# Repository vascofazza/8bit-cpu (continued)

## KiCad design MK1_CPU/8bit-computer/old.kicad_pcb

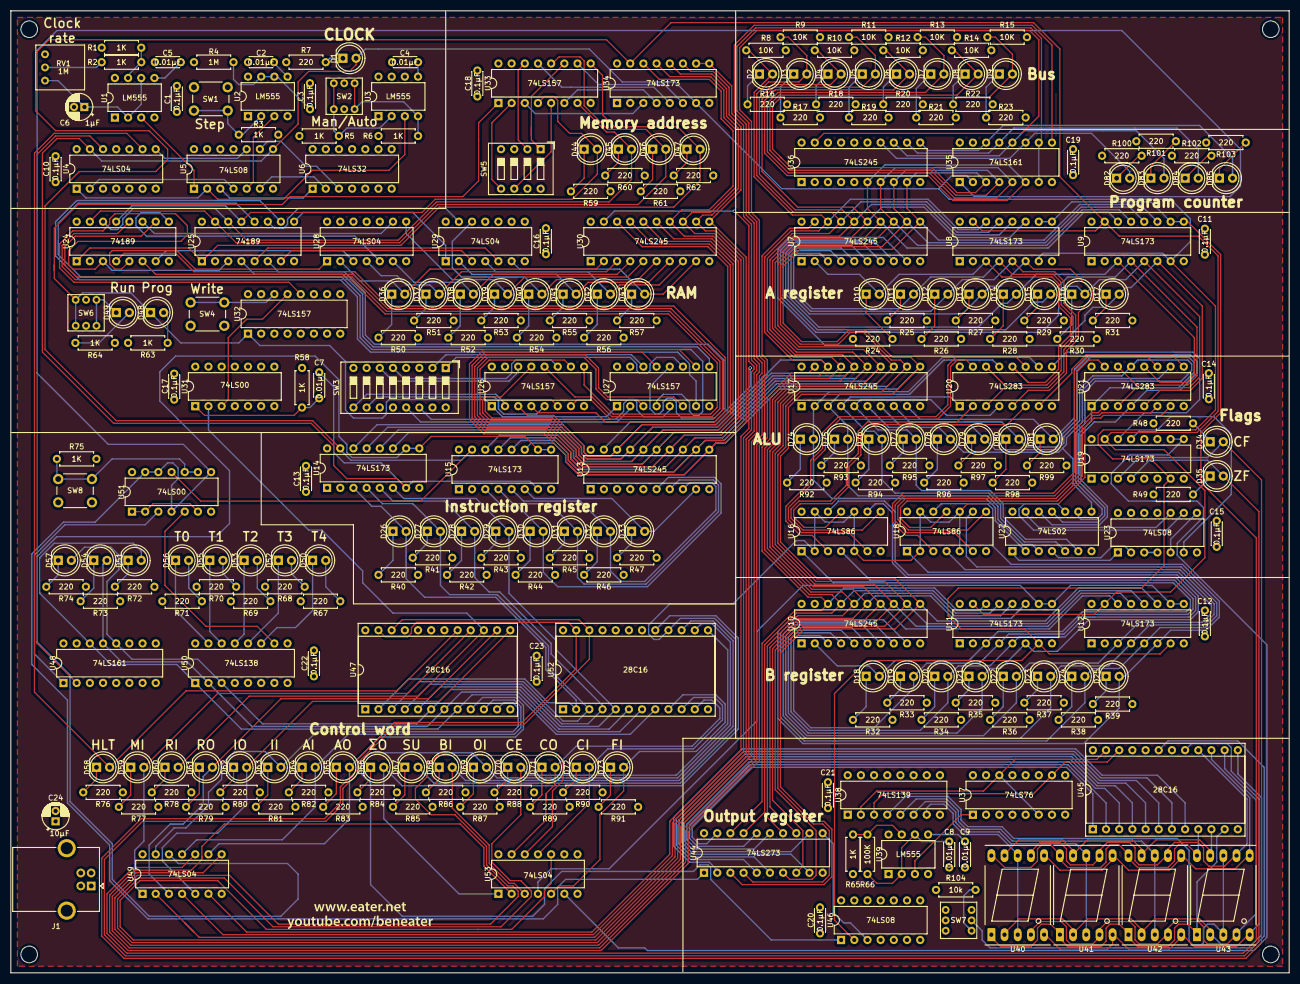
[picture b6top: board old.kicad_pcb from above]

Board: 4 copper layers, 246.4 x 185.4 mm, 277 parts (0 on the bottom side), 290 nets.

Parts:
C1, C3, C10, C11, C12, C13, C14, C15, C16, C17, C18, C19, C20, C21, C22, C23: 0.1µF; C_Disc_D4.3mm_W1.9mm_P5.00mm
C2, C4, C5, C7, C8, C9: 0.01µF; C_Disc_D4.3mm_W1.9mm_P5.00mm
C6: 1µF; CP_Radial_D5.0mm_P2.00mm
C24: 10µF; CP_Radial_D5.0mm_P2.00mm
D1, D26, D27, D28, D29, D58, D59, D60, D61, D62, D63, D64, D65, D66, D67, D68, D69, D70, D71, D72, D73: BLUE; LED_D5.0mm
D2, D3, D4, D5, D6, D7, D8, D9, D10, D11, D12, D13, D14, D15, D16, D17, D18, D19, D20, D21, D22, D23, D24, D25, D36, D37, D38, D39, D40, D41, D42, D43, D48, D51, D54, D57, D74, D75, D76, D77, D78, D79, D80, D81: RED; LED_D5.0mm
D30, D31, D32, D33, D44, D45, D46, D47: YELLOW; LED_D5.0mm
D34, D35, D49, D50, D52, D53, D55, D56, D82, D83, D84, D85: GREEN; LED_D5.0mm
J1: USB_B; USB_B_OST_USB-B1HSxx_Horizontal
R1, R2, R3, R5, R6, R58, R63, R64, R65, R75: 1K; R_Axial_DIN0207_L6.3mm_D2.5mm_P7.62mm_Horizontal
R4: 1M; R_Axial_DIN0207_L6.3mm_D2.5mm_P7.62mm_Horizontal
R7, R16, R17, R18, R19, R20, R21, R22, R23, R24, R25, R26, R27, R28, R29, R30, R31, R32, R33, R34, R35, R36, R37, R38, R39, R40, R41, R42, R43, R44, R45, R46, R47, R48, R49, R50, R51, R52, R53, R54, R55, R56, R57, R59, R60, R61, R62, R67, R68, R69, R70, R71, R72, R73, R74, R76, R77, R78, R79, R80, R81, R82, R83, R84, R85, R86, R87, R88, R89, R90, R91, R92, R93, R94, R95, R96, R97, R98, R99, R100, R101, R102, R103: 220; R_Axial_DIN0207_L6.3mm_D2.5mm_P7.62mm_Horizontal
R8, R9, R10, R11, R12, R13, R14, R15: 10K; R_Axial_DIN0207_L6.3mm_D2.5mm_P7.62mm_Horizontal
R66: 100K; R_Axial_DIN0207_L6.3mm_D2.5mm_P7.62mm_Horizontal
R104: 10k; R_Axial_DIN0207_L6.3mm_D2.5mm_P7.62mm_Horizontal
RV1: 1M; Potentiometer-5.5mm
SW1, SW4: SW_Push; SW_PUSH_6mm_H5mm
SW2, SW6, SW7: SW_SPDT; DPDT-pushbutton
SW3: SW_DIP_x08; SW_DIP_SPSTx08_Slide_9.78x22.5mm_W7.62mm_P2.54mm
SW5: SW_DIP_x04; SW_DIP_SPSTx04_Slide_9.78x12.34mm_W7.62mm_P2.54mm
SW8: Reset; SW_PUSH_6mm_H5mm
U1, U2, U3, U39: LM555; DIP-8_W7.62mm
U4, U28, U29, U49, U53: 74LS04; DIP-14_W7.62mm
U5, U23, U46: 74LS08; DIP-14_W7.62mm
U6: 74LS32; DIP-14_W7.62mm
U7, U10, U13, U17, U30, U36: 74LS245; DIP-20_W7.62mm
U8, U9, U11, U12, U14, U15, U19, U34: 74LS173; DIP-16_W7.62mm
U16, U18: 74LS86; DIP-14_W7.62mm
U20, U21: 74LS283; DIP-16_W7.62mm
U22: 74LS02; DIP-14_W7.62mm
U24, U25: 74189; DIP-16_W7.62mm
U26, U27, U32, U33: 74LS157; DIP-16_W7.62mm
U31, U51: 74LS00; DIP-14_W7.62mm
U35, U48: 74LS161; DIP-16_W7.62mm
U37: 74LS76; DIP-16_W7.62mm
U38: 74LS139; DIP-16_W7.62mm
U40, U41, U42, U43: 7SEGMENT_CC; 7SegmentLED_LTS6760_LTS6780
U44: 74LS273; DIP-20_W7.62mm
U45, U47, U52: 28C16; DIP-24_W15.24mm_Socket
U50: 74LS138; DIP-16_W7.62mm
svg2mod: G***; BenEater

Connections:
/A register/A_0: D17.2, U7.9, U9.6, U21.5
/A register/A_1: D16.2, U7.8, U9.5, U21.3
/A register/A_2: D15.2, U7.7, U9.4, U21.14
/A register/A_3: D14.2, U7.6, U9.3, U21.12
/A register/A_4: D13.2, U7.5, U8.6, U20.5
/A register/A_5: D12.2, U7.4, U8.5, U20.3
/A register/A_6: D11.2, U7.3, U8.4, U20.14
/A register/A_7: D10.2, U7.2, U8.3, U20.12
/A register/BUS_0: D9.2, R15.1, U7.11, U9.11, U10.11, U12.11, U13.11, U15.11, U17.11, U27.10, U30.11, U34.11, U35.3, U36.9, U44.3
/A register/BUS_1: D8.2, R14.1, U7.12, U9.12, U10.12, U12.12, U13.12, U15.12, U17.12, U27.13, U30.12, U34.12, U35.4, U36.8, U44.4
/A register/BUS_2: D7.2, R13.1, U7.13, U9.13, U10.13, U12.13, U13.13, U15.13, U17.13, U27.6, U30.13, U34.13, U35.5, U36.7, U44.7
/A register/BUS_3: D6.2, R12.1, U7.14, U9.14, U10.14, U12.14, U13.14, U15.14, U17.14, U27.3, U30.14, U34.14, U35.6, U36.6, U44.8
/A register/BUS_4: D5.2, R11.1, U7.15, U8.11, U10.15, U11.11, U13.15, U14.11, U17.15, U26.10, U30.15, U44.13
/A register/BUS_5: D4.2, R10.1, U7.16, U8.12, U10.16, U11.12, U13.16, U14.12, U17.16, U26.13, U30.16, U44.14
/A register/BUS_6: D3.2, R9.1, U7.17, U8.13, U10.17, U11.13, U13.17, U14.13, U17.17, U26.6, U30.17, U44.17
/A register/BUS_7: D2.2, R8.1, U7.18, U8.14, U10.18, U11.14, U13.18, U14.14, U17.18, U26.3, U30.18, U44.18
/A register/CLK: C7.1, D1.2, U4.13, U5.8, U8.7, U9.7, U11.7, U12.7, U14.7, U15.7, U19.7, U34.7, U35.2, U46.2
/A register/CLR: U8.15, U9.15, U11.15, U12.15, U14.15, U15.15, U19.15, U34.15, U51.11
/A register/~AI: U8.9, U8.10, U9.9, U9.10, U49.10
/A register/~AO: U7.19, U49.8
/ALU/B_0: D25.2, U10.9, U12.6, U18.12
/ALU/B_1: D24.2, U10.8, U12.5, U18.9
/ALU/B_2: D23.2, U10.7, U12.4, U18.4
/ALU/B_3: D22.2, U10.6, U12.3, U18.1
/ALU/B_4: D21.2, U10.5, U11.6, U16.12
/ALU/B_5: D20.2, U10.4, U11.5, U16.9
/ALU/B_6: D19.2, U10.3, U11.4, U16.4
/ALU/B_7: D18.2, U10.2, U11.3, U16.1
/ALU/CF: D34.2, U19.3, U47.23, U52.23
/ALU/SU: D67.2, U16.2, U16.5, U16.10, U16.13, U18.2, U18.5, U18.10, U18.13, U21.7, U52.16
/ALU/ZF: D35.2, U19.4, U47.22, U52.22
/ALU/~EO: U17.19, U53.2
/ALU/~FI: U19.9, U19.10, U53.6
/B register/~BI: U11.9, U11.10, U12.9, U12.10, U53.4
/Clock/HLT: D58.2, U4.9, U47.17
/Clock/~CLK: U4.12, U48.2
/Control logic/CE: D70.2, U35.7, U35.10, U52.13
/Control logic/IR_4: D29.2, U14.6, U47.5, U52.5
/Control logic/IR_5: D28.2, U14.5, U47.4, U52.4
/Control logic/IR_6: D27.2, U14.4, U47.3, U52.3
/Control logic/IR_7: D26.2, U14.3, U47.2, U52.2
/Control logic/OI: D69.2, U46.1, U52.14
/Control logic/RI: D60.2, U31.2, U47.15
/Control logic/~CLR: U35.1, U44.1, U51.4, U51.8, U51.12, U51.13
/Control logic/~CO: U36.19, U53.12
/Control logic/~II: U14.9, U14.10, U15.9, U15.10, U49.12
/Control logic/~IO: U13.19, U49.6
/Control logic/~J: U35.9, U53.10
/Control logic/~MI: U34.9, U34.10, U49.2
/Control logic/~RO: U30.19, U49.4
/MAR/A0: D47.2, U24.1, U25.1, U33.9
/MAR/A1: D46.2, U24.15, U25.15, U33.12
/MAR/A2: D45.2, U24.14, U25.14, U33.7
/MAR/A3: D44.2, U24.13, U25.13, U33.4
/MAR/PROG: D48.1, SW6.1, U26.1, U27.1, U32.1, U33.1
GND: C1.2, C2.2, C3.2, C4.2, C5.2, C6.2, C8.2, C9.2, C10.2, C11.2, C12.2, C13.2, C14.2, C15.2, C16.2, C17.2, C18.2, C19.2, C20.2, C21.2, C22.2, C23.2, C24.2, J1.4, J1.5, R7.2, R8.2, R9.2, R10.2, R11.2, R12.2, R13.2, R14.2, R15.2, R16.2, R17.2, R18.2, R19.2, R20.2, R21.2, R22.2, R23.2, R24.2, R25.2, R26.2, R27.2, R28.2, R29.2, R30.2, R31.2, R32.2, R33.2, R34.2, R35.2, R36.2, R37.2, R38.2, R39.2, R40.2, R41.2, R42.2, R43.2, R44.2, R45.2, R46.2, R47.2, R48.1, R49.1, R50.2, R51.2, R52.2, R53.2, R54.2, R55.2, R56.2, R57.2, R58.1, R59.2, R60.2, R61.2, R62.2, R72.2, R73.2, R74.2, R75.2, R76.2, R77.2, R78.2, R79.2, R80.2, R81.2, R82.2, R83.2, R84.2, R85.2, R86.2, R87.2, R88.2, R89.2, R90.2, R91.2, R92.2, R93.2, R94.2, R95.2, R96.2, R97.2, R98.2, R99.2, R100.1, R101.1, R102.1, R103.1, R104.2, SW1.1, SW2.2, SW3.3, SW3.4, SW3.7, SW3.8, SW3.11, SW3.12, SW3.15, SW3.16, SW4.1, SW5.3, SW5.4, SW5.7, SW5.8, SW6.2, U1.1, U2.1, U3.1, U3.6, U4.7, U5.7, U6.7, U7.10, U8.1, U8.2, U8.8, U9.1, U9.2, U9.8, U10.10, U11.1, U11.2, U11.8, U12.1, U12.2, U12.8, U13.2, U13.3, U13.4, U13.5, U13.10, U14.1, U14.2, U14.8, U15.1, U15.2, U15.8, U16.7, U17.10, U18.7, U19.1, U19.2, U19.8, U20.8, U21.8, U22.7, U23.7, U24.2, U24.8, U25.2, U25.8, U26.8, U26.15, U27.8, U27.15, U28.7, U29.7, U30.10, U31.7, U32.8, U32.15, U33.8, U33.15, U34.1, U34.2, U34.8, U35.8, U36.1, U36.10, U37.13, U38.1, U38.8, U39.1, U44.10, U45.12, U45.18, U45.20, U46.7, U47.1, U47.12, U47.18, U47.19, U47.20, U48.8, U49.7, U50.4, U50.5, U50.8, U51.7, U52.12, U52.18, U52.19, U52.20, U53.7
unnamed: C2.1, U2.5
unnamed: C3.1, R4.2, U2.6, U2.7
unnamed: C4.1, U3.5
unnamed: C5.1, U1.5
unnamed: C6.1, RV1.1, U1.2, U1.6
unnamed: C7.2, R58.2, U31.1
unnamed: C8.1, R66.2, U39.2, U39.6
unnamed: C9.1, U39.5
unnamed: D1.1, R7.1
unnamed: D2.1, R16.1
unnamed: D3.1, R17.1
unnamed: D4.1, R18.1
unnamed: D5.1, R19.1
unnamed: D6.1, R20.1
unnamed: D7.1, R21.1
unnamed: D8.1, R22.1
unnamed: D9.1, R23.1
unnamed: D10.1, R24.1
unnamed: D11.1, R25.1
unnamed: D12.1, R26.1
unnamed: D13.1, R27.1
unnamed: D14.1, R28.1
unnamed: D15.1, R29.1
unnamed: D16.1, R30.1
unnamed: D17.1, R31.1
unnamed: D18.1, R32.1
unnamed: D19.1, R33.1
unnamed: D20.1, R34.1
unnamed: D21.1, R35.1
unnamed: D22.1, R36.1
unnamed: D23.1, R37.1
unnamed: D24.1, R38.1
unnamed: D25.1, R39.1
unnamed: D26.1, R40.1
unnamed: D27.1, R41.1
unnamed: D28.1, R42.1
unnamed: D29.1, R43.1
unnamed: D30.1, R44.1
unnamed: D30.2, U13.6, U15.3
unnamed: D31.1, R45.1
unnamed: D31.2, U13.7, U15.4
unnamed: D32.1, R46.1
unnamed: D32.2, U13.8, U15.5
unnamed: D33.1, R47.1
unnamed: D33.2, U13.9, U15.6
unnamed: D34.1, R48.2
unnamed: D35.1, R49.2
unnamed: D36.1, R50.1
unnamed: D36.2, U28.2, U30.2
unnamed: D37.1, R51.1
unnamed: D37.2, U28.4, U30.3
unnamed: D38.1, R52.1
unnamed: D38.2, U28.6, U30.4
unnamed: D39.1, R53.1
unnamed: D39.2, U28.8, U30.5
unnamed: D40.1, R54.1
unnamed: D40.2, U29.12, U30.6
unnamed: D41.1, R55.1
unnamed: D41.2, U29.2, U30.7
unnamed: D42.1, R56.1
unnamed: D42.2, U29.4, U30.8
unnamed: D43.1, R57.1
unnamed: D43.2, U29.6, U30.9
unnamed: D44.1, R59.1
unnamed: D45.1, R60.1
unnamed: D46.1, R61.1
unnamed: D47.1, R62.1
unnamed: D48.2, R63.2
unnamed: D49.1, SW6.3
unnamed: D49.2, R64.2
unnamed: D50.1, U50.11
unnamed: D50.2, R67.2
unnamed: D51.1, R72.1
unnamed: D51.2, U47.8, U48.14, U50.1, U52.8
unnamed: D52.1, U50.12
unnamed: D52.2, R68.2
unnamed: D53.1, U50.13
unnamed: D53.2, R69.2
unnamed: D54.1, R73.1
unnamed: D54.2, U47.7, U48.13, U50.2, U52.7
unnamed: D55.1, U50.14
unnamed: D55.2, R70.2
unnamed: D56.1, U50.15
unnamed: D56.2, R71.2
unnamed: D57.1, R74.1
unnamed: D57.2, U47.6, U48.12, U50.3, U52.6
unnamed: D58.1, R76.1
unnamed: D59.1, R77.1
unnamed: D59.2, U47.16, U49.1
unnamed: D60.1, R78.1
unnamed: D61.1, R79.1
unnamed: D61.2, U47.14, U49.3
unnamed: D62.1, R80.1
unnamed: D62.2, U47.13, U49.5
unnamed: D63.1, R81.1
unnamed: D63.2, U47.11, U49.13
unnamed: D64.1, R82.1
unnamed: D64.2, U47.10, U49.11
unnamed: D65.1, R83.1
unnamed: D65.2, U47.9, U49.9
unnamed: D66.1, R84.1
unnamed: D66.2, U52.17, U53.1
unnamed: D67.1, R85.1
unnamed: D68.1, R86.1
unnamed: D68.2, U52.15, U53.3
unnamed: D69.1, R87.1
unnamed: D70.1, R88.1
unnamed: D71.1, R89.1
unnamed: D71.2, U52.11, U53.13
unnamed: D72.1, R90.1
unnamed: D72.2, U52.10, U53.11
unnamed: D73.1, R91.1
unnamed: D73.2, U52.9, U53.5
unnamed: D74.1, R92.1
unnamed: D74.2, U17.2, U20.10, U22.2
unnamed: D75.1, R93.1
unnamed: D75.2, U17.3, U20.13, U22.3
unnamed: D76.1, R94.1
unnamed: D76.2, U17.4, U20.1, U22.5
unnamed: D77.1, R95.1
unnamed: D77.2, U17.5, U20.4, U22.6
unnamed: D78.1, R96.1
unnamed: D78.2, U17.6, U21.10, U22.8
unnamed: D79.1, R97.1
unnamed: D79.2, U17.7, U21.13, U22.9
unnamed: D80.1, R98.1
unnamed: D80.2, U17.8, U21.1, U22.11
unnamed: D81.1, R99.1
unnamed: D81.2, U17.9, U21.4, U22.12
unnamed: D82.1, R100.2
unnamed: D82.2, U35.11, U36.14
unnamed: D83.1, R101.2
unnamed: D83.2, U35.12, U36.13
unnamed: D84.1, R102.2
unnamed: D84.2, U35.13, U36.12
unnamed: D85.1, R103.2
unnamed: D85.2, U35.14, U36.11
unnamed: R1.2, R2.2, U1.7
unnamed: R2.1, RV1.2
unnamed: R3.2, SW1.2, U2.2
unnamed: R5.2, SW2.1, U3.2
unnamed: R6.2, SW2.3, U3.4
unnamed: R65.2, R66.1, U39.7
unnamed: R75.1, SW8.1, U51.9, U51.10
unnamed: R104.1, SW7.1
unnamed: SW3.1, U27.11
unnamed: SW3.2, U27.14
unnamed: SW3.5, U26.11
unnamed: SW3.6, U26.14
unnamed: SW3.9, U26.2
unnamed: SW3.10, U26.5
unnamed: SW3.13, U27.2
unnamed: SW3.14, U27.5
unnamed: SW4.2, U32.14
unnamed: SW5.1, U33.11
unnamed: SW5.2, U33.14
unnamed: SW5.5, U33.2
unnamed: SW5.6, U33.5
unnamed: SW7.2, U45.19
unnamed: U1.3, U5.1
unnamed: U2.3, U5.5
unnamed: U3.3, U4.1, U5.2
unnamed: U4.2, U5.4
unnamed: U4.8, U5.10
unnamed: U5.3, U6.1
unnamed: U5.6, U6.2
unnamed: U5.9, U6.3
unnamed: U16.3, U20.11
unnamed: U16.6, U20.15
unnamed: U16.8, U20.2
unnamed: U16.11, U20.6
unnamed: U18.3, U21.11
unnamed: U18.6, U21.15
unnamed: U18.8, U21.2
unnamed: U18.11, U21.6
unnamed: U19.13, U23.6
unnamed: U19.14, U20.9
unnamed: U20.7, U21.9
unnamed: U22.1, U23.1
unnamed: U22.4, U23.2
unnamed: U22.10, U23.9
unnamed: U22.13, U23.10
unnamed: U23.3, U23.4
unnamed: U23.5, U23.8
unnamed: U24.3, U25.3, U32.12
unnamed: U24.4, U26.4
unnamed: U24.5, U28.1
unnamed: U24.6, U26.7
unnamed: U24.7, U28.3
unnamed: U24.9, U28.5
unnamed: U24.10, U26.12
unnamed: U24.11, U28.9
unnamed: U24.12, U26.9
unnamed: U25.4, U27.9
unnamed: U25.5, U29.5
unnamed: U25.6, U27.12
unnamed: U25.7, U29.3
unnamed: U25.9, U29.1
unnamed: U25.10, U27.7
unnamed: U25.11, U29.13
unnamed: U25.12, U27.4
unnamed: U31.3, U32.13
unnamed: U33.3, U34.3
unnamed: U33.6, U34.4
unnamed: U33.10, U34.6
unnamed: U33.13, U34.5
unnamed: U37.1, U39.3
unnamed: U37.10, U38.3, U45.22
unnamed: U37.6, U37.14, U38.2, U45.23
unnamed: U38.4, U43.3, U43.8
unnamed: U38.5, U42.3, U42.8
unnamed: U38.6, U41.3, U41.8
unnamed: U38.7, U40.3, U40.8
unnamed: U40.1, U41.1, U42.1, U43.1, U45.11
unnamed: U40.2, U41.2, U42.2, U43.2, U45.13
unnamed: U40.4, U41.4, U42.4, U43.4, U45.14
unnamed: U40.5, U41.5, U42.5, U43.5, U45.17
unnamed: U40.6, U41.6, U42.6, U43.6, U45.15
unnamed: U40.7, U41.7, U42.7, U43.7, U45.16
unnamed: U40.9, U41.9, U42.9, U43.9, U45.10
unnamed: U40.10, U41.10, U42.10, U43.10, U45.9
unnamed: U44.2, U45.8
unnamed: U44.5, U45.7
unnamed: U44.6, U45.6
unnamed: U44.9, U45.5
unnamed: U44.11, U46.3
unnamed: U44.12, U45.4
unnamed: U44.15, U45.3
unnamed: U44.16, U45.2
unnamed: U44.19, U45.1
unnamed: U48.1, U51.3
unnamed: U50.10, U51.5
unnamed: U51.1, U51.2, U51.6
VCC: C1.1, C10.1, C11.1, C12.1, C13.1, C14.1, C15.1, C16.1, C17.1, C18.1, C19.1, C20.1, C21.1, C22.1, C23.1, C24.1, J1.1, R1.1, R3.1, R4.1, R5.1, R6.1, R63.1, R64.1, R65.1, R67.1, R68.1, R69.1, R70.1, R71.1, SW7.3, SW8.2, U1.4, U1.8, U2.4, U2.8, U3.8, U4.14, U5.14, U6.14, U7.1, U7.20, U8.16, U9.16, U10.1, U10.19, U10.20, U11.16, U12.16, U13.1, U13.20, U14.16, U15.16, U16.14, U17.1, U17.20, U18.14, U19.16, U20.16, U21.16, U22.14, U23.14, U24.16, U25.16, U26.16, U27.16, U28.14, U29.14, U30.1, U30.20, U31.14, U32.16, U33.16, U34.16, U35.16, U36.20, U37.2, U37.3, U37.4, U37.5, U37.7, U37.8, U37.9, U37.12, U37.16, U38.16, U39.8, U44.20, U45.21, U45.24, U46.14, U47.21, U47.24, U48.7, U48.9, U48.10, U48.16, U49.14, U50.6, U50.16, U51.14, U52.1, U52.21, U52.24, U53.14

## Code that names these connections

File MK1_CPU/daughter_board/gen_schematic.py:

#!/usr/bin/env python3
"""Generate KiCad 8 schematic for MK1 I2C/SPI/Speaker daughter board."""
import uuid

def uid():
    return str(uuid.uuid4())

# Component positions (mm)
J4_X, J4_Y = 30, 80
U1_X, U1_Y = 90, 60     # 74HC574
U2_X, U2_Y = 90, 140    # 74HC126
Q1_X, Q1_Y = 160, 50    # 2N7000 (SDA open-drain, for future I2C read)
Q2_X, Q2_Y = 160, 90    # NPN speaker driver
BZ_X, BZ_Y = 190, 90    # Piezo

header = f'''(kicad_sch
  (version 20231120)
  (generator "mk1_daughter_gen")
  (generator_version "1.0")
  (uuid "{uid()}")
  (paper "A4")
  (title_block
    (title "MK1 Daughter Board — I2C/SPI/Speaker")
    (date "2026-03-30")
    (rev "1.0")
    (comment 1 "Write-only I2C + SPI read/write + Piezo speaker")
    (comment 2 "Plugs into J4 external interface connector"))
'''

# We'll create a simplified schematic with text labels showing connections
# rather than trying to place actual KiCad library symbols (which require
# exact library paths that vary per installation)

# Instead, create a comprehensive netlist + wiring guide as a KiCad-compatible
# text schematic with hierarchical labels

labels_and_notes = f'''
  (text "MK1 DAUGHTER BOARD SCHEMATIC\\n\\n\
J4 CONNECTOR (from MK1)\\n\
Pin 1,6: E0 (read strobe)\\n\
Pin 3: BUS_2\\n\
Pin 5: BUS_6\\n\
Pin 7: BUS_1\\n\
Pin 8: GND\\n\
Pin 11: BUS_4\\n\
Pin 12: E1 (write strobe)\\n\
Pin 15: BUS_3\\n\
Pin 17: BUS_5\\n\
Pin 18: BUS_7\\n\\n\
74HC574 (U1) - Output Latch\\n\
CLK = E1 (J4 pin 12)\\n\
OE = GND (always enabled)\\n\
D7 = BUS_7, D6 = BUS_6, D5 = BUS_5\\n\
D4 = BUS_4, D3 = BUS_3, D2 = BUS_2, D1 = BUS_1\\n\
Q7 = SPI_MOSI -> EEPROM SI\\n\
Q6 = SPI_SCK -> EEPROM SCK\\n\
Q5 = SPI_CS -> EEPROM ~CS\\n\
Q4 = I2C_SDA -> LCD SDA (+ 4.7K pull-up)\\n\
Q3 = I2C_SCL -> LCD SCL (+ 4.7K pull-up)\\n\
Q2 = SPEAKER -> NPN base (1K) -> piezo\\n\
Q1,Q0 = spare\\n\\n\
74HC126 (U2) - Input Buffer\\n\
OE1 = E0 (J4 pin 1) — active HIGH\\n\
A1 = EEPROM SO (MISO)\\n\
Y1 = BUS_7 (J4 pin 18) — read back via exr(0)\\n\
Gates 2-4: spare\\n\\n\
SOFTWARE:\\n\
I2C write: exw(val, 1, 0) — bit4=SDA, bit3=SCL\\n\
SPI write: exw(val, 1, 0) — bit7=MOSI, bit6=SCK, bit5=~CS\\n\
SPI read:  exr(0) — bit7=MISO\\n\
Speaker:   toggle bit2 in exw loop"
    (at 30 30 0)
    (effects
      (font
        (size 1.5 1.5))
      (justify left)))
)
'''

with open('/Users/gadyke/8bit-cpu/MK1_CPU/daughter_board/daughter_board.kicad_sch', 'w') as f:
    f.write(header)
    f.write(labels_and_notes)

print("Generated daughter_board.kicad_sch")
print("\nThis is a text-annotation schematic. For a proper schematic,")
print("create a new KiCad project and add these components:")
print()
print("NETLIST:")
print("=" * 60)
print()
print("J4 (2x9 connector from MK1)")
print("  Pin 1,6  (E0)    -> U2 pin 1 (OE1)")
print("  Pin 3    (BUS_2) -> U1 pin 3 (D2)")
print("  Pin 5    (BUS_6) -> U1 pin 7 (D6)")
print("  Pin 7    (BUS_1) -> U1 pin 2 (D1)")
print("  Pin 8    (GND)   -> U1 pin 10, U2 pin 7, GND rail")
print("  Pin 11   (BUS_4) -> U1 pin 5 (D4)")
print("  Pin 12   (E1)    -> U1 pin 11 (CLK)")
print("  Pin 15   (BUS_3) -> U1 pin 4 (D3)")
print("  Pin 17   (BUS_5) -> U1 pin 6 (D5)")
print("  Pin 18   (BUS_7) -> U1 pin 8 (D7), U2 pin 3 (Y1)")
print()
print("U1: 74HC574 (DIP-20)")
print("  Pin 1  (OE)  -> GND (always enabled)")
print("  Pin 2  (D0)  -> GND (BUS_0 not on J4)")
print("  Pin 3  (D1)  -> J4 pin 7 (BUS_1)")
print("  Pin 4  (D2)  -> J4 pin 3 (BUS_2)")
print("  Pin 5  (D3)  -> J4 pin 15 (BUS_3)")
print("  Pin 6  (D4)  -> J4 pin 11 (BUS_4)")
print("  Pin 7  (D5)  -> J4 pin 17 (BUS_5)")
print("  Pin 8  (D6)  -> J4 pin 5 (BUS_6)")
print("  Pin 9  (D7)  -> J4 pin 18 (BUS_7)")
print("  Pin 10 (GND) -> GND")
print("  Pin 11 (CLK) -> J4 pin 12 (E1)")
print("  Pin 12 (Q7)  -> SPI MOSI (EEPROM SI)")
print("  Pin 13 (Q6)  -> SPI SCK (EEPROM SCK)")
print("  Pin 14 (Q5)  -> SPI ~CS (EEPROM ~CS)")
print("  Pin 15 (Q4)  -> I2C SDA + 4.7K pull-up to VCC")
print("  Pin 16 (Q3)  -> I2C SCL + 4.7K pull-up to VCC")
print("  Pin 17 (Q2)  -> 1K -> Q2 base (NPN speaker driver)")
print("  Pin 18 (Q1)  -> spare")
print("  Pin 19 (Q0)  -> spare")
print("  Pin 20 (VCC) -> VCC + 100nF decoupling to GND")
print()
print("U2: 74HC126 (DIP-14)")
print("  Pin 1  (OE1) -> J4 pin 1 or 6 (E0)")
print("  Pin 2  (A1)  -> EEPROM SO (MISO)")
print("  Pin 3  (Y1)  -> J4 pin 18 (BUS_7)")
print("  Pin 4  (OE2) -> GND (disabled) or future use")
print("  Pin 5  (A2)  -> future input")
print("  Pin 6  (Y2)  -> future output")
print("  Pin 7  (GND) -> GND")
print("  Pin 8  (Y3)  -> future")
print("  Pin 9  (A3)  -> future")
print("  Pin 10 (OE3) -> GND (disabled)")
print("  Pin 11 (Y4)  -> future")
print("  Pin 12 (A4)  -> future")
print("  Pin 13 (OE4) -> GND (disabled)")
print("  Pin 14 (VCC) -> VCC + 100nF decoupling to GND")
print()
print("Q2: NPN transistor (2N2222 / BC547)")
print("  Base     -> 1K resistor -> U1 pin 17 (Q2)")
print("  Collector -> Piezo (+) ")
print("  Emitter  -> GND")
print("  Piezo (-) -> VCC")
print()
print("SPI EEPROM (e.g., 25LC256 / AT25256)")
print("  ~CS  -> U1 pin 14 (Q5)")
print("  SO   -> U2 pin 2 (A1)")
print("  SI   -> U1 pin 12 (Q7)")
print("  SCK  -> U1 pin 13 (Q6)")
print("  VCC  -> VCC")
print("  GND  -> GND")
print("  ~WP  -> VCC (write enabled)")
print("  ~HOLD -> VCC (not held)")
print()
print("I2C LCD (1602A with PCF8574 backpack)")
print("  SDA -> U1 pin 15 (Q4) + 4.7K pull-up to VCC")
print("  SCL -> U1 pin 16 (Q3) + 4.7K pull-up to VCC")
print("  VCC -> VCC")
print("  GND -> GND")
print()
print("POWER: VCC not on J4 — tap from MK1 5V rail")
print("       or bodge wire to J4 pin 9 (NC)")

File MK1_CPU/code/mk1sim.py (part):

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            # SD + SO is OK for PUSH: you WANT the pre-decrement address.
            # Register output mux codes: DO=1, BO=2, SO=3, AO=4, PO=5, CO=6, EO=7
            reg_out = (step & _REG_OUT_MASK) >> _REG_OUT_SHIFT
            if (step & SU) and reg_out == 3:  # SU + SO = 011 = 3
                errors.append(
                    f"0x{opcode:02X} '{mnemonic}' step {i}: SU combined with SO — "
                    f"SO reads pre-increment value (use separate steps like POP does)"
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            # Rule 5: EI and EO in the same step (feedback through ALU)
            # Register input mux codes: DI=1, BI=2, EI=3, AI=4, SI=5, CI=6, PI=7
            reg_in = (step & _REG_IN_MASK) >> _REG_IN_SHIFT
            if reg_in == 3 and reg_out == 7:  # EI=011=3, EO=111=7
                warnings.append(
                    f"0x{opcode:02X} '{mnemonic}' step {i}: EI and EO in same step — "
                    f"ALU feedback (works if setup time is met, but risky)"
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        self.cycle += 1

        # Get current microcode step
        flags_irq = (0 << 3) | (0 << 2) | (self.ZF << 1) | self.CF  # IRQ0=0, IRQ1=0
        ctrl = ucode[flags_irq][self.IR][1][self.step & 7]
        self.current_ctrl = ctrl

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    code2[pc] = decode['move $c, $b']; pc += 1
    code2[pc] = 0; pc += 1
    code2[pc] = decode['move imm, $pc']; code2[pc+1] = loop_addr // 2; pc += 2
    code2[pc] = decode['hlt']; pc += 1
    # This is getting complicated with the addressing. Let's skip the fibonacci test
    # and focus on the unit tests above.

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    code = assemble_simple([
        (decode['move imm, $a'], 5),
        (decode['move imm, $b'], 5),
        decode['sub $b, $a'],      # A = 0, ZF=1
        (decode['jnz'], 10),       # should NOT jump (ZF=1)
        decode['move $a, $out'],   # display 0
        decode['hlt'],
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    code = assemble_simple([
        (decode['move imm, $a'], 5),
        (decode['move imm, $b'], 3),
        decode['sub $b, $a'],      # A = 2, ZF=0
        (decode['jnz'], 10),       # SHOULD jump (ZF=0)
        (decode['move imm, $a'], 99),  # skipped
        decode['move $a, $out'],   # addr 10: display 2
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    def emit2(opcode, imm=None):
        nonlocal pc
        code[pc] = opcode; pc += 1
        code[pc] = imm if imm is not None else 0; pc += 1
    JAL = 0xAC; RET_OP = 0x6C
    emit2(decode['move imm, $a'], 77)
    emit2(JAL, 8)                  # call addr 8
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    def emit(opcode, imm=None):
        nonlocal pc
        code[pc] = opcode; pc += 1
        code[pc] = imm if imm is not None else 0; pc += 1

    # push $a = stor $a, [$sp] = (0b10 << 6) | (0 << 3) | 4 = 0x84
    PUSH_A = 0x84
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    code_adc[8] = 0x39; code_adc[9] = 0       # ldi $b, 0
    code_adc[10] = 0xC1; code_adc[11] = 0     # adc (A = 44 + 0 + CF(1) = 45)
    code_adc[12] = 0x06; code_adc[13] = 0     # out (45)
    code_adc[14] = 0x7F; code_adc[15] = 0     # hlt
    results.append(run_test("ADC: 200+100=44(CF=1), then ADC 0 = 45", code_adc, [44, 45]))

    # ── Test: SBC (subtract with borrow) ──
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    code_sbc = bytearray(256)
    code_sbc[0] = 0x38; code_sbc[1] = 50      # ldi $a, 50
    code_sbc[2] = 0x39; code_sbc[3] = 100     # ldi $b, 100
    code_sbc[4] = 0xD4; code_sbc[5] = 0       # sub $b,$a (A=206, CF=0)
    code_sbc[6] = 0x06; code_sbc[7] = 0       # out (206)
    code_sbc[8] = 0x39; code_sbc[9] = 0       # ldi $b, 0
    code_sbc[10] = 0xC2; code_sbc[11] = 0     # sbc (A = 206 - 0 - 1 = 205)
    code_sbc[12] = 0x06; code_sbc[13] = 0     # out (205)
    code_sbc[14] = 0x7F; code_sbc[15] = 0     # hlt
    results.append(run_test("SBC: 50-100=206(CF=0), then SBC 0 = 205", code_sbc, [206, 205]))

    # ── Test: TST (non-destructive bit test) ──
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    code_tst[6] = 0xFF; code_tst[7] = 0x02    # tst 2 (test bit 1 — clear, ZF=1)
    # After tst 2: A AND 2 = 0xA5 & 0x02 = 0. ZF=1. A still 0xA5.
    code_tst[8] = 0x06; code_tst[9] = 0       # out (still 165)
    code_tst[10] = 0x7F; code_tst[11] = 0     # hlt
    results.append(run_test("TST: non-destructive bit test (A preserved)", code_tst, [165, 165]))

    # ── Test: OUT_IMM (output immediate without touching A) ──
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    code_oi[0] = 0x38; code_oi[1] = 99        # ldi $a, 99
    code_oi[2] = 0xD1; code_oi[3] = 42        # out_imm 42 (displays 42, A stays 99)
    code_oi[4] = 0x06; code_oi[5] = 0         # out (displays A = 99)
    code_oi[6] = 0x7F; code_oi[7] = 0         # hlt
    results.append(run_test("OUT_IMM: output 42 then A(99)", code_oi, [42, 99]))

    # ── Test: JAL_R (indirect call via register A) ──
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    code_jr = bytearray(256)
    code_jr[0] = 0x38; code_jr[1] = 10        # ldi $a, 10
    code_jr[2] = 0xE1; code_jr[3] = 0         # jal_r (push ret, PC = A = 10)
    code_jr[4] = 0x7F; code_jr[5] = 0         # hlt (return lands here)
    # Subroutine at address 10:
    code_jr[10] = 0x38; code_jr[11] = 77      # ldi $a, 77
    code_jr[12] = 0x06; code_jr[13] = 0       # out
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    code_ew[0] = 0x38; code_ew[1] = 0x42    # ldi $a, 0x42
    code_ew[2] = 0x1F; code_ew[3] = 0       # exw 1 1 (A drives bus, external latch)
    code_ew[4] = 0x06; code_ew[5] = 0       # out (A should still be 0x42)
    code_ew[6] = 0x7F; code_ew[7] = 0       # hlt
    cpu_ew.load_program(code_ew)
    cpu_ew.run()
    ok_ew = cpu_ew.output_history == [0x42] and cpu_ew.A == 0x42
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    code_gr[0] = 0x38; code_gr[1] = 0xFF    # ldi $a, 0xFF
    code_gr[2] = 0x79; code_gr[3] = 0       # exr 1 0 (A = bus value, 0 in sim)
    code_gr[4] = 0x06; code_gr[5] = 0       # out
    code_gr[6] = 0x7F; code_gr[7] = 0       # hlt
    cpu_gr.load_program(code_gr)
    cpu_gr.run()
    ok_gr = cpu_gr.A != 0xFF
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    # Main program at addr 10:
    code_oc[10] = 0xDF; code_oc[11] = 5       # ocall 5 (A=5, push ret, PC=0)
    code_oc[12] = 0x06; code_oc[13] = 0       # out (A after return — should be 5)
    code_oc[14] = 0x7F; code_oc[15] = 0       # hlt
    cpu_oc = MK1()
    cpu_oc.load_program(code_oc)
    cpu_oc.PC = 10  # start execution from addr 10
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    code_pb[6] = 0x39; code_pb[7] = 0           # ldi $b, 0 (clobber B)
    code_pb[8] = 0xF2; code_pb[9] = 0           # pop_b (B = 42)
    code_pb[10] = 0x06; code_pb[11] = 0         # out (A should still be 99)
    code_pb[12] = 0x7F; code_pb[13] = 0         # hlt
    cpu_pb.load_program(code_pb)
    cpu_pb.run()
    ok_pb = cpu_pb.B == 42 and cpu_pb.output_history == [99]
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    code_d2[0] = 0x38; code_d2[1] = 20         # ldi $a, 20
    code_d2[2] = 0xDD; code_d2[3] = 0          # deref2 (A = stack[A] = stack[20] = 0x77)
    code_d2[4] = 0x06; code_d2[5] = 0          # out
    code_d2[6] = 0x7F; code_d2[7] = 0          # hlt
    cpu_d2.load_program(code_d2)
    cpu_d2.run()
    ok_d2 = cpu_d2.output_history == [0x77]
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    code_id2[6] = 0x38; code_id2[7] = 50       # ldi $a, 50
    code_id2[8] = 0xDD; code_id2[9] = 0        # deref2 (A = stack[50] = 0xAB)
    code_id2[10] = 0x06; code_id2[11] = 0      # out
    code_id2[12] = 0x7F; code_id2[13] = 0      # hlt
    cpu_id2.load_program(code_id2)
    cpu_id2.run()
    ok_id2 = cpu_id2.output_history == [0xAB]
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
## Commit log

2020-03-29 fixup
2020-03-30 readme and license
2020-03-30 bus_breakout schematics
2020-03-30 MK1 V1 project
2020-03-30 helix display interface project
2020-03-30 start9 programming interface project
2020-03-30 README
2020-03-30 version 2.0
2020-04-04 timing fix
2020-04-04 pdf schematics
2020-04-10 resistor label update
2020-04-10 signals
2020-04-11 microcode for v2
2020-04-17 2.0b hardware revision
2020-04-17 microcode 2.0b review
2020-04-17 v2.0b code uploader review
2020-04-17 README.md update
2020-04-17 helix display interface code
2020-04-17 eeprom programmer
2020-04-17 cpu-definition, assembler and example programs
2020-04-21 microcode revision 2.0d
2020-04-21 assembler cpu definition
2020-04-21 revision 2.0d
2020-04-21 schematics revision 2.0d
2020-04-21 cpu definition revision 2.0d
2020-04-21 programs refactoring
2020-04-21 helix display library
2020-04-23 PCB tracks revision
2020-04-23 start9
2020-04-23 quick/merge/bubble sorts
2020-04-25 programs, libraries and CPU definition optimization
2020-04-25 programming interface software
2020-04-26 schematics cleanup
2022-01-05 Add extended version of output_display.py script
    Based on the display_multiplex sketch, to create an image for those of us that don't program EEPROM with Arduino.
2022-01-21 Add XOR function to standard library
    I'm sure this can be optimised significantly, but here's a readable XOR function to complete the set
2022-01-30 Schematic for a "native" MK1->Character display
2022-01-31 Example code for "native" LCD interface
2022-12-12 Update cpu instruction definition and asm programs for customasm v0.11
    #bits in global scope
    #bankdef and #bank ".data"/".instr" is now bare data/instr
    consistent indenting in #bankdef
    nested #tokendef is now #subruledef, in global scope
    #cpudef is now #ruledef
    token/subrule def "=" is now "=>"
2022-12-12 Switch git submodule for customasm to current upstream main branch
